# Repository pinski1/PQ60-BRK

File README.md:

#PQ60-BRK
A breakout board for PQ60 compatible Pocket Qubes.

The PQ60 Breakout board is a development board for pico-satellites. It connects to the PQ60 bus and breaks the signals into two headers. This allows for fast prototyping of new system boards.

Uses @Pinski1's [PQ60-Template](https://github.com/pinski1/PQ60-Template) as the starting point for the design.

##Features
* 2off 2x10way 0.1" pitch headers with the PQ60 signals
* 7x10way 0.1" pitch prototyping thru-hole grid

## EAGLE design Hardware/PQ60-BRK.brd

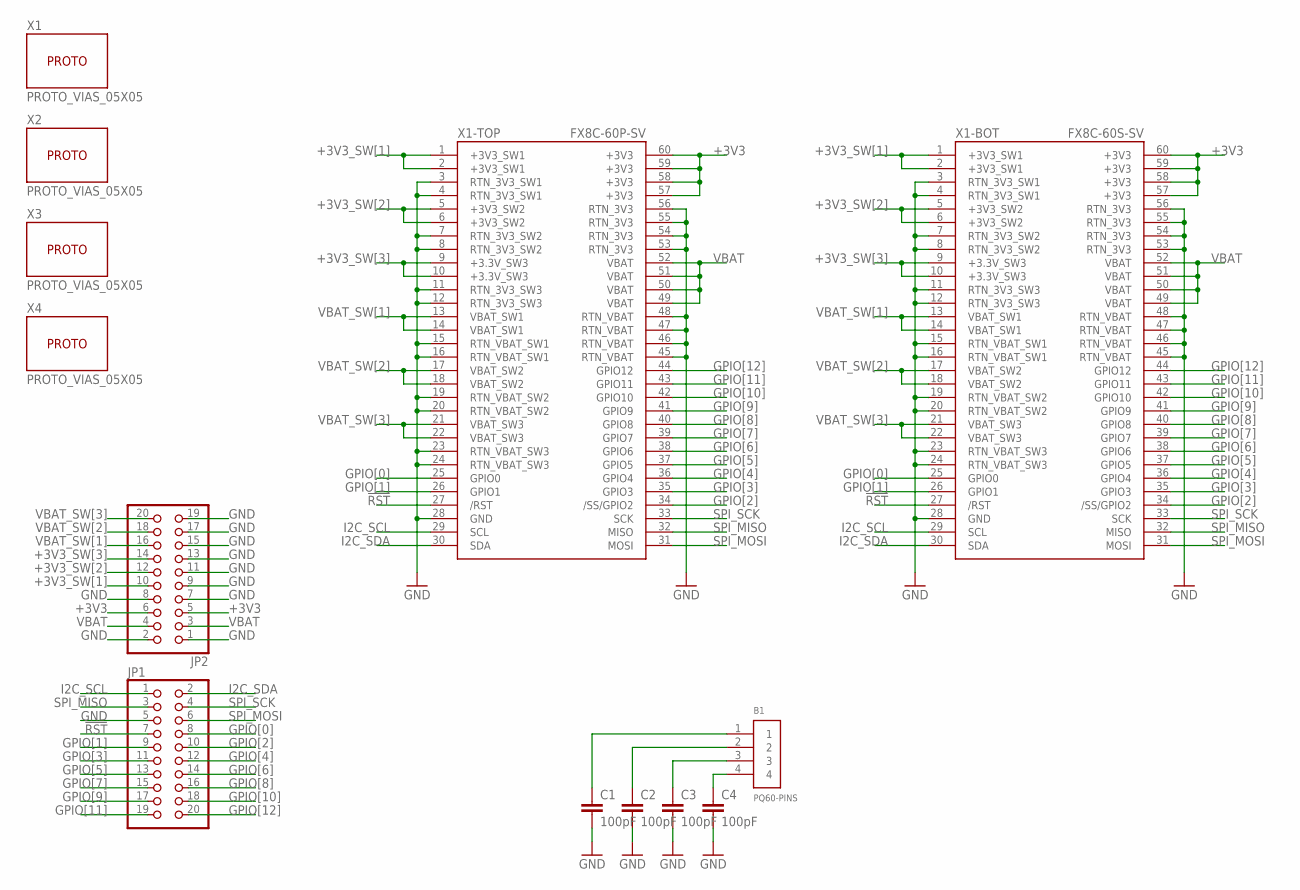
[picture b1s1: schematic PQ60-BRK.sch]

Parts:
B1: PQ60-PINS; PQ60_PINS
C1, C2, C3, C4: 100pF; C0402; MPN MC0402B101K250CT
JP1, JP2: PINHD-2X10; 2X10
X1, X2, X3, X4: PROTO_VIAS_05X05
X1-BOT: FX8C-60S-SV; MPN FX8C-60S-SV5(91)
X1-TOP: FX8C-60P-SV; MPN FX8C-60P-SV1(91)

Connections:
!RST: JP1.7, X1-BOT.27 (/RST), X1-TOP.27 (/RST)
+3V3: JP2.5, JP2.6, X1-BOT.57 (+3V3), X1-BOT.58 (+3V3), X1-BOT.59 (+3V3), X1-BOT.60 (+3V3), X1-TOP.57 (+3V3), X1-TOP.58 (+3V3), X1-TOP.59 (+3V3), X1-TOP.60 (+3V3)
+3V3_SW[1]: JP2.10, X1-BOT.1 (+3V3_SW1), X1-BOT.2 (+3V3_SW1), X1-TOP.1 (+3V3_SW1), X1-TOP.2 (+3V3_SW1)
+3V3_SW[2]: JP2.12, X1-BOT.5 (+3V3_SW2), X1-BOT.6 (+3V3_SW2), X1-TOP.5 (+3V3_SW2), X1-TOP.6 (+3V3_SW2)
+3V3_SW[3]: JP2.14, X1-BOT.9 (+3.3V_SW3), X1-BOT.10 (+3.3V_SW3), X1-TOP.9 (+3.3V_SW3), X1-TOP.10 (+3.3V_SW3)
GND: C1.2, C2.2, C3.2, C4.2, JP1.5, JP2.1, JP2.2, JP2.7, JP2.8, JP2.9, JP2.11, JP2.13, JP2.15, JP2.17, JP2.19, X1-BOT.3 (RTN_3V3_SW1), X1-BOT.4 (RTN_3V3_SW1), X1-BOT.7 (RTN_3V3_SW2), X1-BOT.8 (RTN_3V3_SW2), X1-BOT.11 (RTN_3V3_SW3), X1-BOT.12 (RTN_3V3_SW3), X1-BOT.15 (RTN_VBAT_SW1), X1-BOT.16 (RTN_VBAT_SW1), X1-BOT.19 (RTN_VBAT_SW2), X1-BOT.20 (RTN_VBAT_SW2), X1-BOT.23 (RTN_VBAT_SW3), X1-BOT.24 (RTN_VBAT_SW3), X1-BOT.28 (GND), X1-BOT.45 (RTN_VBAT), X1-BOT.46 (RTN_VBAT), X1-BOT.47 (RTN_VBAT), X1-BOT.48 (RTN_VBAT), X1-BOT.53 (RTN_3V3), X1-BOT.54 (RTN_3V3), X1-BOT.55 (RTN_3V3), X1-BOT.56 (RTN_3V3), X1-TOP.3 (RTN_3V3_SW1), X1-TOP.4 (RTN_3V3_SW1), X1-TOP.7 (RTN_3V3_SW2), X1-TOP.8 (RTN_3V3_SW2), X1-TOP.11 (RTN_3V3_SW3), X1-TOP.12 (RTN_3V3_SW3), X1-TOP.15 (RTN_VBAT_SW1), X1-TOP.16 (RTN_VBAT_SW1), X1-TOP.19 (RTN_VBAT_SW2), X1-TOP.20 (RTN_VBAT_SW2), X1-TOP.23 (RTN_VBAT_SW3), X1-TOP.24 (RTN_VBAT_SW3), X1-TOP.28 (GND), X1-TOP.45 (RTN_VBAT), X1-TOP.46 (RTN_VBAT), X1-TOP.47 (RTN_VBAT), X1-TOP.48 (RTN_VBAT), X1-TOP.53 (RTN_3V3), X1-TOP.54 (RTN_3V3), X1-TOP.55 (RTN_3V3), X1-TOP.56 (RTN_3V3)
GPIO[0]: JP1.8, X1-BOT.25 (GPIO0), X1-TOP.25 (GPIO0)
GPIO[1]: JP1.9, X1-BOT.26 (GPIO1), X1-TOP.26 (GPIO1)
GPIO[2]: JP1.10, X1-BOT.34 (/SS/GPIO2), X1-TOP.34 (/SS/GPIO2)
GPIO[3]: JP1.11, X1-BOT.35 (GPIO3), X1-TOP.35 (GPIO3)
GPIO[4]: JP1.12, X1-BOT.36 (GPIO4), X1-TOP.36 (GPIO4)
GPIO[5]: JP1.13, X1-BOT.37 (GPIO5), X1-TOP.37 (GPIO5)
GPIO[6]: JP1.14, X1-BOT.38 (GPIO6), X1-TOP.38 (GPIO6)
GPIO[7]: JP1.15, X1-BOT.39 (GPIO7), X1-TOP.39 (GPIO7)
GPIO[8]: JP1.16, X1-BOT.40 (GPIO8), X1-TOP.40 (GPIO8)
GPIO[9]: JP1.17, X1-BOT.41 (GPIO9), X1-TOP.41 (GPIO9)
GPIO[10]: JP1.18, X1-BOT.42 (GPIO10), X1-TOP.42 (GPIO10)
GPIO[11]: JP1.19, X1-BOT.43 (GPIO11), X1-TOP.43 (GPIO11)
GPIO[12]: JP1.20, X1-BOT.44 (GPIO12), X1-TOP.44 (GPIO12)
I2C_SCL: JP1.1, X1-BOT.29 (SCL), X1-TOP.29 (SCL)
I2C_SDA: JP1.2, X1-BOT.30 (SDA), X1-TOP.30 (SDA)
unnamed: B1.1, C1.1
unnamed: B1.2, C2.1
unnamed: B1.3, C3.1
unnamed: B1.4, C4.1
SPI_MISO: JP1.3, X1-BOT.32 (MISO), X1-TOP.32 (MISO)
SPI_MOSI: JP1.6, X1-BOT.31 (MOSI), X1-TOP.31 (MOSI)
SPI_SCK: JP1.4, X1-BOT.33 (SCK), X1-TOP.33 (SCK)
VBAT: JP2.3, JP2.4, X1-BOT.49 (VBAT), X1-BOT.50 (VBAT), X1-BOT.51 (VBAT), X1-BOT.52 (VBAT), X1-TOP.49 (VBAT), X1-TOP.50 (VBAT), X1-TOP.51 (VBAT), X1-TOP.52 (VBAT)
VBAT_SW[1]: JP2.16, X1-BOT.13 (VBAT_SW1), X1-BOT.14 (VBAT_SW1), X1-TOP.13 (VBAT_SW1), X1-TOP.14 (VBAT_SW1)
VBAT_SW[2]: JP2.18, X1-BOT.17 (VBAT_SW2), X1-BOT.18 (VBAT_SW2), X1-TOP.17 (VBAT_SW2), X1-TOP.18 (VBAT_SW2)
VBAT_SW[3]: JP2.20, X1-BOT.21 (VBAT_SW3), X1-BOT.22 (VBAT_SW3), X1-TOP.21 (VBAT_SW3), X1-TOP.22 (VBAT_SW3)

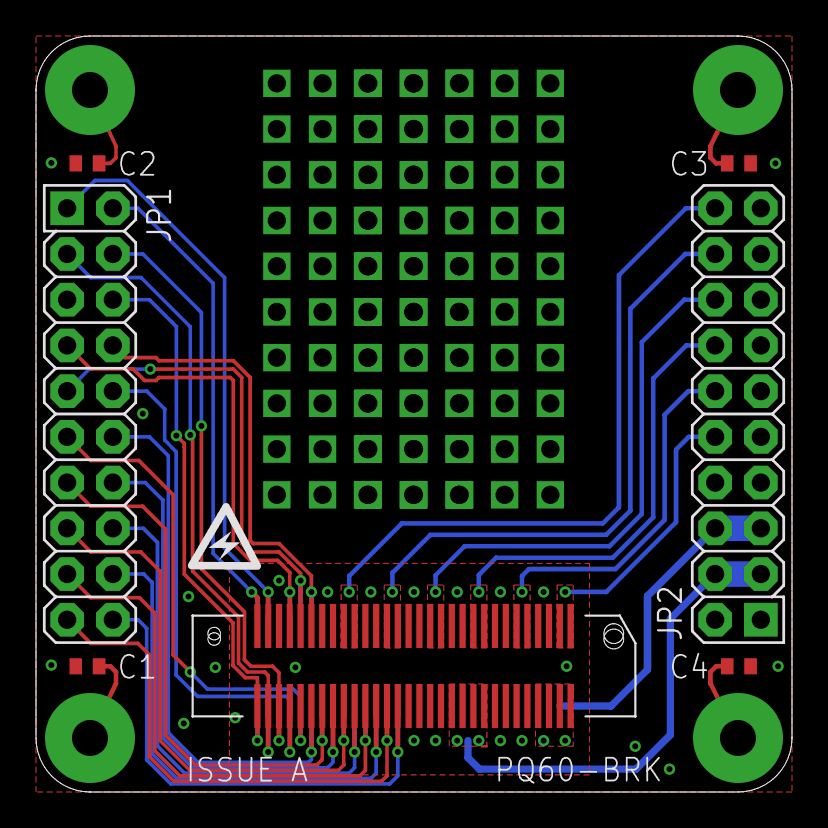
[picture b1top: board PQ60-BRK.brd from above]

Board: 2 copper layers, 42.0 x 42.0 mm, 13 parts (1 on the bottom side), 32 nets.

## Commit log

2015-09-03 Initial Checkin
2015-09-22 Adding PCB images.
2015-09-22 optimised images

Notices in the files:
parts and their libraries:
SparkFun-Connectors: Licensing: Creative Commons ShareAlike 4.0 International - https://creativecommons.org/licenses/by-sa/4.0
